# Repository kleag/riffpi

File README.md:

# RiffPi

RiffPi is the control daemon for **Kleag's MFX**, a DIY guitar multi-effect pedalboard built
around a Raspberry Pi, a [Pisound](https://blokas.io/pisound/) sound card, and
[Guitarix](https://guitarix.org/) as the effects engine. It reads the pedalboard's foot
switches, rotary encoders, keypad, joystick, and expression pedal, and turns them into MIDI
sent to Guitarix.

**Full documentation: <https://kleag.github.io/riffpi/>**

## Features

- 4 foot switches with LEDs toggle Guitarix effects, and stay in sync if Guitarix changes state
  on its own (e.g. loading a preset).
- 4 rotary encoders send relative MIDI CC changes; the last one's button cycles preset banks A-D.
- A 4x4 keypad selects presets directly and doubles as mouse left/right click.
- A joystick moves the mouse pointer, for fine-tuning Guitarix's on-screen knobs, and its push
  acts as a middle click.
- An expression pedal sends a smoothed, continuous MIDI CC.
- Hardware design (KiCad) for the controller PCB, in [`kicad_board/`](kicad_board/).

## Quick start

```bash
pip install riffpi
riffpi install-service   # writes, enables, and starts a systemd --user service
```

See [Installation](https://kleag.github.io/riffpi/installation/) for the full Raspberry Pi
setup (I2C, `uinput` permissions, installing and autostarting Guitarix and its guitariqx GUI, headless/no-login boot,
WiFi power management), and
[Usage](https://kleag.github.io/riffpi/usage/) for what each control does and the full MIDI CC
mapping.

## Hardware

Wiring, MCP23017/ADS1115 pin maps, a block diagram, and the schematic/PCB renders are in
[Architecture](https://kleag.github.io/riffpi/architecture/). Hardware design source (KiCad 9)
is in [`kicad_board/`](kicad_board/).

## Development

```bash
uv build                       # or: python -m build
uvx ruff check src/            # lint
uvx twine check dist/*         # validate package metadata
.venv/bin/mkdocs serve         # preview the docs site locally
uvx bumpver update --minor     # bump the version (patch/minor/major)
```

CI (`.github/workflows/`) lints and builds the package on every push/PR, deploys the docs site
on changes to `docs/`, and publishes to PyPI on GitHub Release.

## License

Copyright Gaël de Chalendar, 2025-2026.

This project describes Open Hardware and is licensed under the CERN-OHL-W v2. You may
redistribute and modify it and make products using it under the terms of the
[CERN-OHL-W v2](https://cern.ch/cern-ohl) — see [`LICENSE.md`](LICENSE.md). It is distributed
WITHOUT ANY EXPRESS OR IMPLIED WARRANTY, INCLUDING OF MERCHANTABILITY, SATISFACTORY QUALITY AND
FITNESS FOR A PARTICULAR PURPOSE.

Source location: <https://github.com/kleag/riffpi>. As per CERN-OHL-W v2 section 4.1, should
you produce hardware based on these sources, you must keep the source location visible on the
external case of the pedal or other product you make using this documentation.

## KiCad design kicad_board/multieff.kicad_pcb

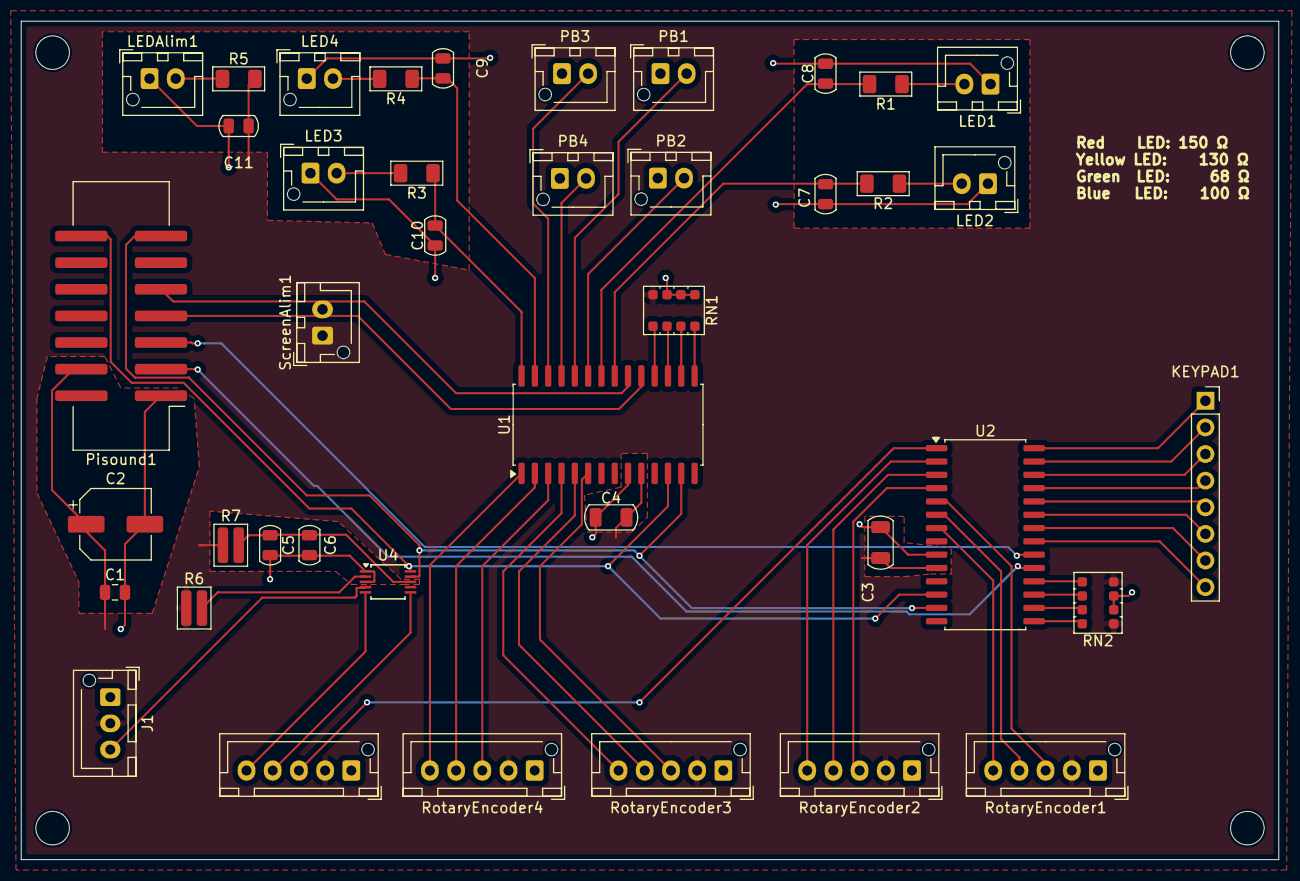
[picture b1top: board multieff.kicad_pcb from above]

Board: 2 copper layers, 120.0 x 80.0 mm, 45 parts (0 on the bottom side), 56 nets.

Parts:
C1: 1uF; C_0805_2012Metric
C2: 100uF; CP_Elec_6.3x5.4
C3, C4: 0.1uF; C_1206_3216Metric
C5: 0.1uF; C_0805_2012Metric
C6: 10uF; C_0805_2012Metric
C7, C8, C9, C10, C11: 47uF; C_0805_2012Metric
H1, H2, H3, H4: MountingHole; MountingHole_3.2mm_M3
J1: Wha1; JST_XH_B3B-XH-AM_1x03_P2.50mm_Vertical
Joystick1: Conn_01x05; JST_XH_B5B-XH-AM_1x05_P2.50mm_Vertical
KEYPAD1: Conn_01x08; PinSocket_1x08_P2.54mm_Vertical
LED1, LED2, LED3, LED4: Conn_01x02; JST_XH_B2B-XH-AM_1x02_P2.50mm_Vertical
LEDAlim1: Conn_01x02; JST_XH_B2B-XH-AM_1x02_P2.50mm_Vertical
PB1, PB2, PB3, PB4: Conn_01x02; JST_XH_B2B-XH-AM_1x02_P2.50mm_Vertical
Pisound1: Conn_02x07_Odd_Even; IDC-Header_2x07_P2.54mm_Vertical_SMD
R1: 150; R_1206_3216Metric_Pad1.30x1.75mm_HandSolder
R2: 130; R_1206_3216Metric_Pad1.30x1.75mm_HandSolder
R3: 68; R_1206_3216Metric_Pad1.30x1.75mm_HandSolder
R4, R5: 100; R_1206_3216Metric_Pad1.30x1.75mm_HandSolder
R6: 10k; R_0612_1632Metric
R7: 10; R_0612_1632Metric
RN1, RN2: 10k; R_Array_Convex_4x1206
RotaryEncoder1, RotaryEncoder2, RotaryEncoder3, RotaryEncoder4: Conn_01x05; JST_XH_B5B-XH-AM_1x05_P2.50mm_Vertical
ScreenAlim1: Conn_01x02; JST_XH_B2B-XH-AM_1x02_P2.50mm_Vertical
U1, U2: MCP23017_SO; SOIC-28W_7.5x17.9mm_P1.27mm
U4: ADS1115IDGS; TSSOP-10_3x3mm_P0.5mm

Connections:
+3.3V: C1.1, C2.1, C3.2, C4.2, C11.1, J1.2, Joystick1.2, Pisound1.4, R5.2, R6.1, R7.1, RN1.4 (R4.1), RN2.1 (R1.1), RN2.4 (R4.1), RotaryEncoder1.2, RotaryEncoder2.2, RotaryEncoder3.2, RotaryEncoder4.2, U1.10 (VSS), U2.10 (VSS)
/5V: Pisound1.2, ScreenAlim1.2
/SCL: Pisound1.14, U1.12 (SCK), U2.12 (SCK), U4.10 (SCL)
/SDA: Pisound1.13, U1.13 (SDA), U2.13 (SDA), U4.9 (SDA)
GND: C1.2, C2.2, C3.1, C4.1, C5.2, C6.2, C7.2, C8.2, C9.1, C10.1, C11.2, J1.1, Joystick1.1, LED1.1, LED2.1, LED3.1, LED4.1, LEDAlim1.1, PB1.1, PB2.1, PB3.1, PB4.1, Pisound1.1, RN1.1 (R1.1), RN1.2 (R2.1), RN1.3 (R3.1), RN2.2 (R2.1), RN2.3 (R3.1), RotaryEncoder1.1, RotaryEncoder2.1, RotaryEncoder3.1, RotaryEncoder4.1, ScreenAlim1.1, U1.9 (VDD), U2.9 (VDD), U4.1 (ADDR), U4.3 (GND)
unnamed: J1.3, U4.4 (AIN0)
unnamed: Joystick1.3, U2.1 (GPB0)
unnamed: Joystick1.4, U4.6 (AIN2)
unnamed: Joystick1.5, U4.5 (AIN1)
unnamed: KEYPAD1.1, U2.28 (GPA7)
unnamed: KEYPAD1.2, U2.27 (GPA6)
unnamed: KEYPAD1.3, U2.26 (GPA5)
unnamed: KEYPAD1.4, U2.25 (GPA4)
unnamed: KEYPAD1.5, U2.24 (GPA3)
unnamed: KEYPAD1.6, U2.23 (GPA2)
unnamed: KEYPAD1.7, U2.22 (GPA1)
unnamed: KEYPAD1.8, U2.21 (GPA0)
unnamed: LED1.2, R1.1
unnamed: LED2.2, R2.1
unnamed: LED3.2, R3.2
unnamed: LED4.2, R4.2
unnamed: LEDAlim1.2, R5.1
unnamed: PB1.2, U1.24 (GPA3)
unnamed: PB2.2, U1.23 (GPA2)
unnamed: PB3.2, U1.26 (GPA5)
unnamed: PB4.2, U1.25 (GPA4)
unnamed: Pisound1.3, U2.19 (INTB)
unnamed: Pisound1.5, U2.20 (INTA)
unnamed: Pisound1.7, U1.19 (INTB)
unnamed: Pisound1.9, U1.20 (INTA)
unnamed: RN1.8 (R1.2), U1.15 (A0)
unnamed: RN1.7 (R2.2), U1.16 (A1)
unnamed: RN1.6 (R3.2), U1.17 (A2)
unnamed: RN1.5 (R4.2), U1.18 (~RESET)
unnamed: RN2.8 (R1.2), U2.15 (A0)
unnamed: RN2.7 (R2.2), U2.16 (A1)
unnamed: RN2.6 (R3.2), U2.17 (A2)
unnamed: RN2.5 (R4.2), U2.18 (~RESET)
unnamed: RotaryEncoder1.3, U2.5 (GPB4)
unnamed: RotaryEncoder1.4, U2.6 (GPB5)
unnamed: RotaryEncoder1.5, U2.7 (GPB6)
unnamed: RotaryEncoder2.3, U2.4 (GPB3)
unnamed: RotaryEncoder2.4, U2.3 (GPB2)
unnamed: RotaryEncoder2.5, U2.2 (GPB1)
unnamed: RotaryEncoder3.3, U1.6 (GPB5)
unnamed: RotaryEncoder3.4, U1.5 (GPB4)
unnamed: RotaryEncoder3.5, U1.4 (GPB3)
unnamed: RotaryEncoder4.3, U1.3 (GPB2)
unnamed: RotaryEncoder4.4, U1.2 (GPB1)
unnamed: RotaryEncoder4.5, U1.1 (GPB0)
unnamed: C7.1, R2.2, U1.21 (GPA0)
unnamed: C8.1, R1.2, U1.22 (GPA1)
unnamed: C9.2, R4.1, U1.27 (GPA6)
unnamed: C10.2, R3.1, U1.28 (GPA7)
unnamed: R6.2, U4.2 (ALERT/RDY)
unnamed: C5.1, C6.1, R7.2, U4.8 (VDD)

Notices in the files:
README.md:
License: CERN-OHL-W-2.0
kicad_board/multieff.kicad_pcb:
Licensed under CERN-OHL-W v2
